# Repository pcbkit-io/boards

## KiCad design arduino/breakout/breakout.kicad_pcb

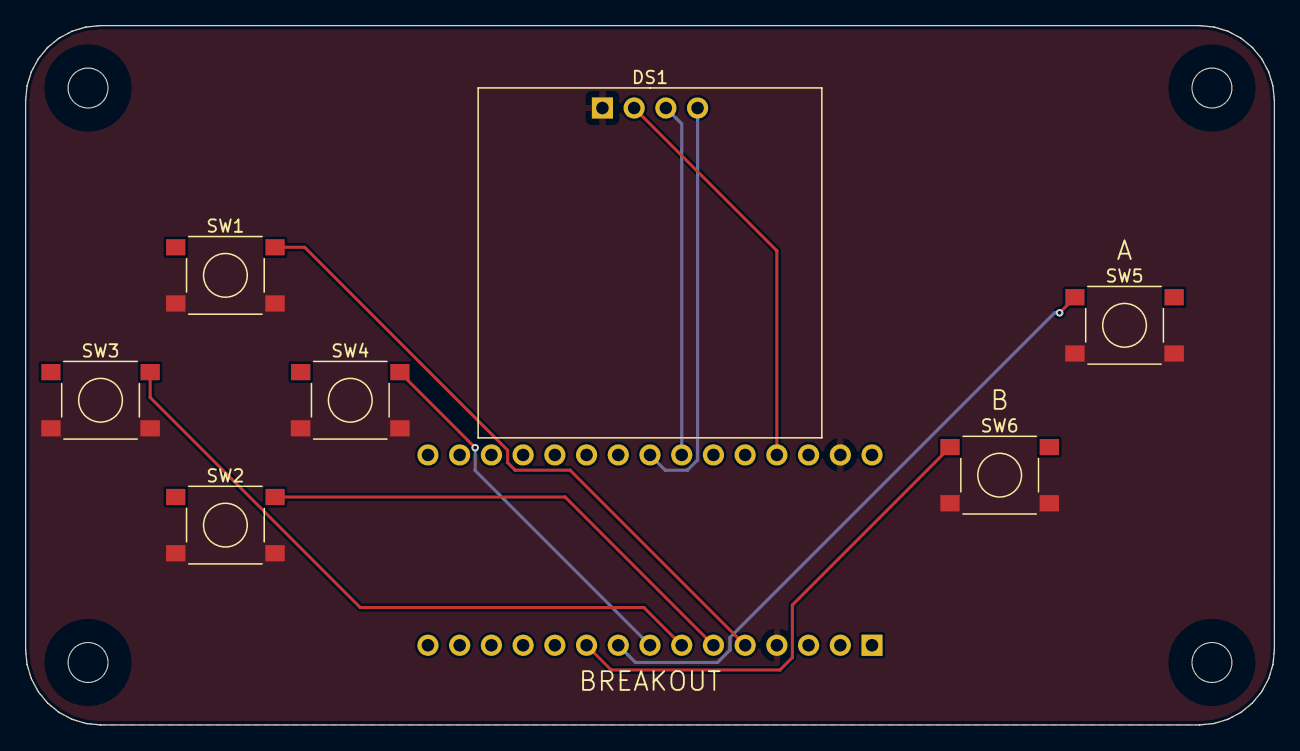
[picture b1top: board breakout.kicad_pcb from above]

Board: 2 copper layers, 100.0 x 56.0 mm, 12 parts (1 on the bottom side), 10 nets.

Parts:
DS1: SSD1306 0.96in 128x64 I2C OLED module; OLED_0.96in_I2C_Socket_1x04_P2.54mm
H1, H2, H3, H4: MountingHole_3.2mm_M3
NANO: A000005; Arduino_Nano_Socket_2x15_P2.54mm_W15.24mm
SW1, SW2, SW3, SW4, SW5, SW6: PTS645SM43SMTR92 LFS; SW_Tactile_SPST_6x6mm_SMD

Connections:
A: NANO.9 (D6), SW5.1 (a)
B: NANO.10 (D7), SW6.1 (a)
DOWN: NANO.6 (D3), SW2.1 (a)
GND: DS1.1 (GND), NANO.4 (GND), NANO.29 (GND), SW1.2 (b), SW2.2 (b), SW3.2 (b), SW4.2 (b), SW5.2 (b), SW6.2 (b)
LEFT: NANO.7 (D4), SW3.1 (a)
RIGHT: NANO.8 (D5), SW4.1 (a)
SCL: DS1.3 (SCL), NANO.24 (A5)
SDA: DS1.4 (SDA), NANO.23 (A4)
UP: NANO.5 (D2), SW1.1 (a)
V5: DS1.2 (VCC), NANO.27 (P5V)

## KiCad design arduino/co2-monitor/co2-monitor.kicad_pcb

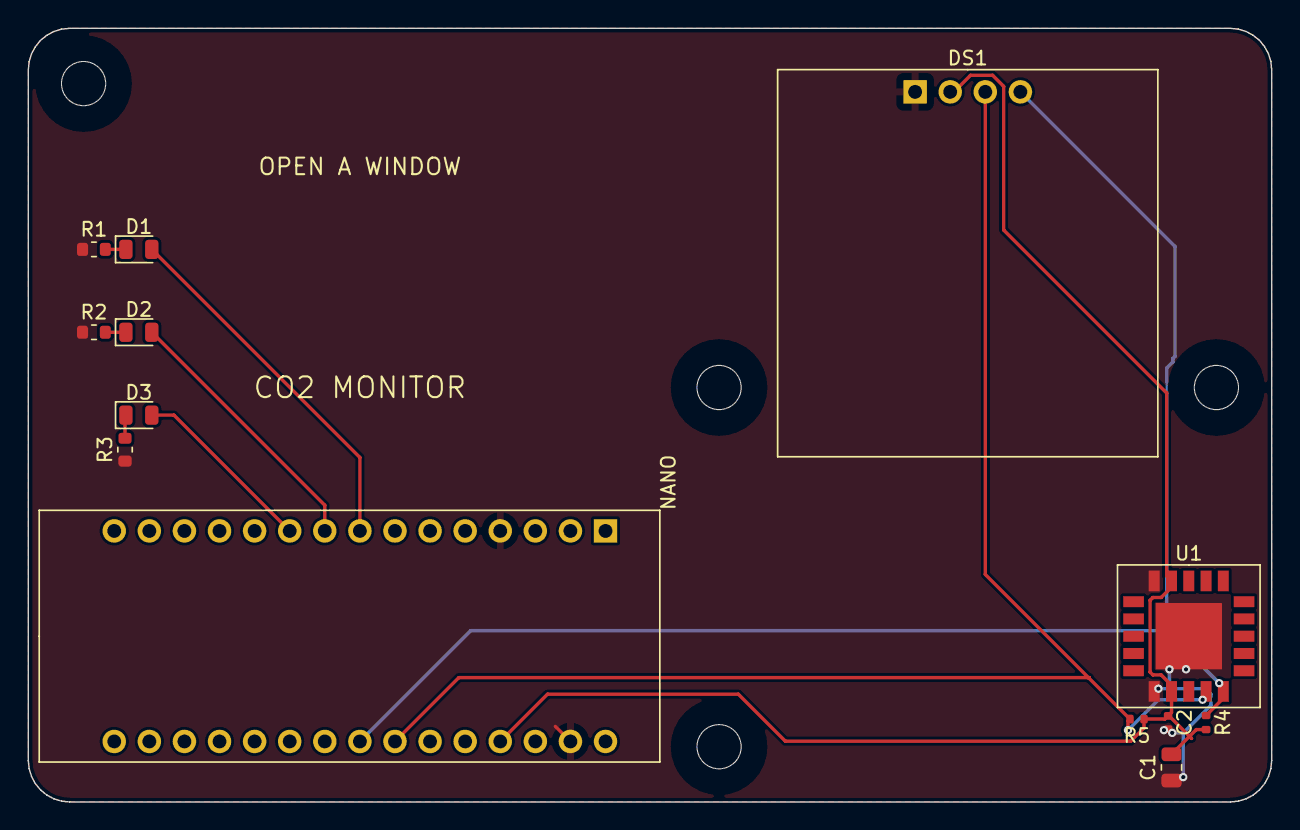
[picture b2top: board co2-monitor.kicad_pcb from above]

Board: 2 copper layers, 90.0 x 56.0 mm, 17 parts (0 on the bottom side), 10 nets.

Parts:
C1: 10uF; C_0805_2012Metric
C2: 100nF; C_0402_1005Metric
D1: green; LED_0805_2012Metric
D2: orange; LED_0805_2012Metric
D3: red; LED_0805_2012Metric
DS1: SSD1306 0.96in 128x64 I2C OLED module; OLED_0.96in_I2C_Socket_1x04_P2.54mm
H1, H2, H3, H4: MountingHole_3.2mm_M3
NANO: A000005; Arduino_Nano_Socket_2x15_P2.54mm_W15.24mm
R1, R2, R3: 1kohm; R_0603_1608Metric
R4, R5: 10kohm; R_0402_1005Metric
U1: SCD40-D-R2; LGA-21_10.1x10.1mm_SCD4x_20_pads_and_a_centre_pad

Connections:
AMBER: D2.2 (A), NANO.9 (D6)
AMBER_K: D2.1 (K), R2.1 (a)
GND: C1.2 (b), C2.2 (b), DS1.1 (GND), NANO.4 (GND), NANO.29 (GND), R1.2 (b), R2.2 (b), R3.2 (b), U1.6 (GND), U1.20 (GND), U1.21 (GND)
GREEN: D1.2 (A), NANO.8 (D5)
GREEN_K: D1.1 (K), R1.1 (a)
RED: D3.2 (A), NANO.10 (D7)
RED_K: D3.1 (K), R3.1 (a)
SCL: DS1.3 (SCL), NANO.24 (A5), R5.2 (b), U1.9 (SCL)
SDA: DS1.4 (SDA), NANO.23 (A4), R4.1 (a), U1.10 (SDA)
V5: C1.1 (a), C2.1 (a), DS1.2 (VCC), NANO.27 (P5V), R4.2 (b), R5.1 (a), U1.7 (VDD), U1.19 (VDDH)

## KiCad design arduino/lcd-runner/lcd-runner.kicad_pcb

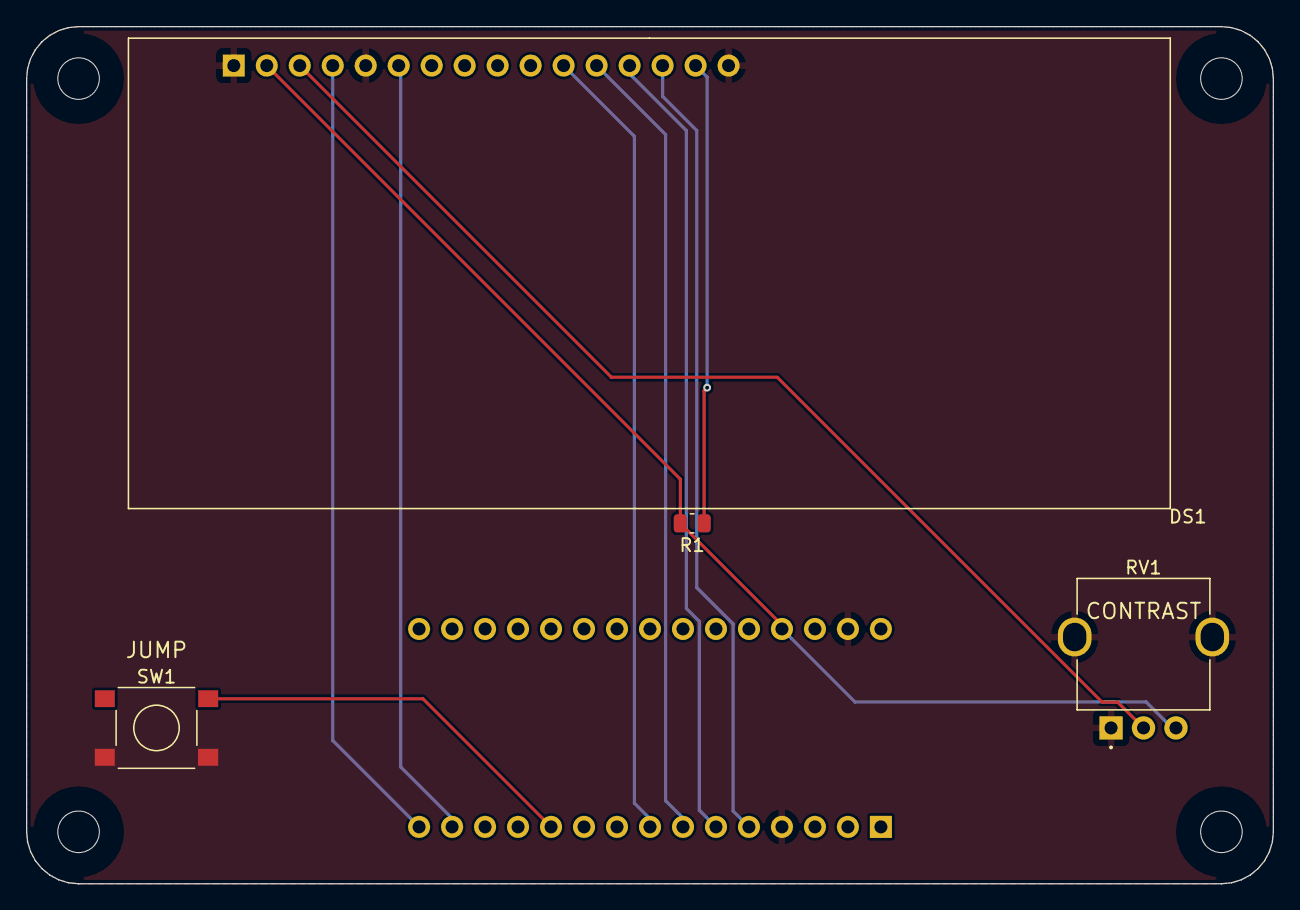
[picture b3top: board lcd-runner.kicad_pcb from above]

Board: 2 copper layers, 96.0 x 66.0 mm, 9 parts (1 on the bottom side), 11 nets.

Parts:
DS1: 1602 16x2 character LCD module (HD44780 compatibl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; LCD_1602_Socket_1x16_P2.54mm
H1, H2, H3, H4: MountingHole_3.2mm_M3
NANO: A000005; Arduino_Nano_Socket_2x15_P2.54mm_W15.24mm
R1: 220ohm; R_0805_2012Metric
RV1: PTV09A-4020F-B103; Potentiometer_Bourns_PTV09A-4_Vertical
SW1: PTS645SM43SMTR92 LFS; SW_Tactile_SPST_6x6mm_SMD

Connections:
D4: DS1.11 (DB4), NANO.8 (D5)
D5: DS1.12 (DB5), NANO.7 (D4)
D6: DS1.13 (DB6), NANO.6 (D3)
D7: DS1.14 (DB7), NANO.5 (D2)
E: DS1.6 (E), NANO.14 (D11)
GND: DS1.1 (VSS), DS1.5 (RW), DS1.16 (K), NANO.4 (GND), NANO.29 (GND), RV1.1 (CCW), RV1.MP, SW1.2 (b)
JUMP: NANO.11 (D8), SW1.1 (a)
LED_A: DS1.15 (A), R1.1 (a)
RS: DS1.4 (RS), NANO.15 (D12)
V0: DS1.3 (V0), RV1.2 (W)
V5: DS1.2 (VDD), NANO.27 (P5V), R1.2 (b), RV1.3 (CW)
